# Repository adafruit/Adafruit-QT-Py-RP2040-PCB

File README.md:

## Adafruit QT Py RP2040 PCB

<a href="http://www.adafruit.com/products/4900"><br/>
Click here to purchase one from the Adafruit shop</a>

PCB files for the Adafruit QT Py RP2040.

Format is EagleCAD schematic and board layout
* https://www.adafruit.com/product/4900

### Description

What a cutie pie! Or is it... a QT Py? This diminutive dev board comes with one of our new favorite chip, the RP2040. It's been made famous in the new Raspberry Pi Pico and our Feather RP2040 and ItsyBitsy RP2040, but what if we wanted something really smol?

A new chip means a new QT Py, and the Raspberry Pi RP2040 is no exception. When we saw this chip we thought "this chip is going to be awesome when we give it the cuuutie QT Py Treatment", and so we did! This QT Py features the RP2040, and all niceties you know and love about the original QT Py

#### Plug-and-play STEMMA QT

The star of the QT Py is our favorite connector - the STEMMA QT, a chainable I2C port that can be used with any of our STEMMA QT sensors and accessories. Having this connector means you don't need to do any soldering to get started.

What can you pop into the QT port? How about OLEDs! Inertial Measurment Units! Sensors a-plenty. All plug-and-play thanks to the innovative chainable design: SparkFun Qwiic-compatible STEMMA QT connectors for the I2C bus so you don't even need to solder. Just plug in a compatible cable and attach it to your MCU of choice, and you’re ready to load up some software and measure some light.

Use any SparkFun Qwiic boards! Seeed Grove I2C boards will also work with this adapter cable.

#### Software Support

At the time of launch, there is no Arduino core support for the chip on this board. There is great C/C++ support, an official MicroPython port, and a CircuitPython port! We of course recommend CircuitPython because we think it's the easiest way to get started and it has support with most of our drivers, displays, sensors, and more, supported out of the box so you can follow along with our CircuitPython projects and tutorials.

#### QT Py RP2040 Specifications

Pinout and shape is Seeed Xiao compatible, with castellated pads so you can solder it to a PCB with a cut out to allow the bottom components some breathing room. In addition to the QT connector, we also added an RGB NeoPixel (with a controllable power pin to allow for ultra-low-power usage), and both boot-mode and reset buttons (great for restarting your program or entering the bootloader). This QT Py comes with loose 0.1" headers you can solder in for breadboard use

While the RP2040 has lots of onboard RAM (264KB), it does not have built-in FLASH memory. Instead, that is provided by the external QSPI flash chip. On this board there is 8MB, which is shared between the program it's running and any file storage used by MicroPython or CircuitPython. When using C/C++ you get the whole flash memory, if using Python you will have about 7 MB remaining for code, files, images, fonts, etc.

* Same size, form-factor, and pin-out as our SAMD-based QT Py
* USB Type C connector - If you have only Micro B cables, this adapter will come in handy!
* RP2040 32-bit Cortex M0+ dual-core running at ~125 MHz @ 3.3V logic and power
* 264 KB RAM
* 8 MB SPI FLASH chip for storing files and CircuitPython/MicroPython code storage. No EEPROM
* Native USB supported by every OS - can be used as USB serial console, MIDI, Keyboard/Mouse HID, even a little disk drive for storing Python scripts.
* Can be used with MicroPython or CircuitPython
* Built-in RGB NeoPixel LED
* 13 GPIO pins (11 breakout pads and two QT pads):
  * Four 12 bit ADCs (one more than Pico)
  * Two I2C ports (one on the QT connector, one on the breakout pads)
  * SPI and UART peripherals, in standard QT Py locations,
  * PWM outputs on every IO pin - for servos, LEDs, etc
  * There are 6 GPIO in consecutive order for PIO compatibility
* 3.3V regulator with 600mA peak output
* 12 MHz crystal
* Both Reset button and Bootloader select buttons for quick restarts (no unplugging-replugging to relaunch code)
* Really really small

#### About the RP2040

Inside the RP2040 is a 'permanent ROM' USB UF2 bootloader. What that means is when you want to program new firmware, you can hold down the BOOT button while plugging it into USB (or pulling down the RUN/Reset pin to ground) and it will appear as a USB disk drive you can drag the firmware onto. Folks who have been using Adafruit products will find this very familiar - we use the technique on all our native-USB boards. Just note you don't double-click reset, instead hold down BOOTSEL during boot to enter the bootloader!

The RP2040 is a powerful chip, which has the clock speed of our M4 (SAMD51), and two cores that are equivalent to our M0 (SAMD21). Since it is an M0 chip, it does not have a floating point unit or DSP hardware support - so if you're doing something with heavy floating point math, it will be done in software and thus not as fast as an M4. For many other computational tasks, you'll get close-to-M4 speeds!

For peripherals, there are two I2C controllers, two SPI controllers, and two UARTs that are multiplexed across the GPIO - check the pinout for what pins can be set to which. There are 16 PWM channels, each pin has a channel it can be set to (ditto on the pinout).

You'll note there's no I2S peripheral, or SDIO, or camera, what's up with that? Well, instead of having specific hardware support for serial-data-like peripherals like these, the RP2040 comes with the PIO state machine system which is a unique and powerful way to create custom hardware logic and data processing blocks that run on their own without taking up a CPU. For example, NeoPixels - often we bitbang the timing-specific protocol for these LEDs. For the RP2040, we instead use PIO object that reads in the data buffer and clocks out the right bitstream with perfect accuracy. Same with I2S audio in or out, LED matrix displays, 8-bit or SPI based TFTs, even VGA! In MicroPython and CircuitPython you can create PIO control commands to script the peripheral and load it in at runtime. There are 2 PIO peripherals with 4 state machines each.

### License

Adafruit invests time and resources providing this open source design, please support Adafruit and open-source hardware by purchasing products from [Adafruit](https://www.adafruit.com)!

Designed by Limor Fried/Ladyada for Adafruit Industries.

Creative Commons Attribution/Share-Alike, all text above must be included in any redistribution.
See license.txt for additional details.

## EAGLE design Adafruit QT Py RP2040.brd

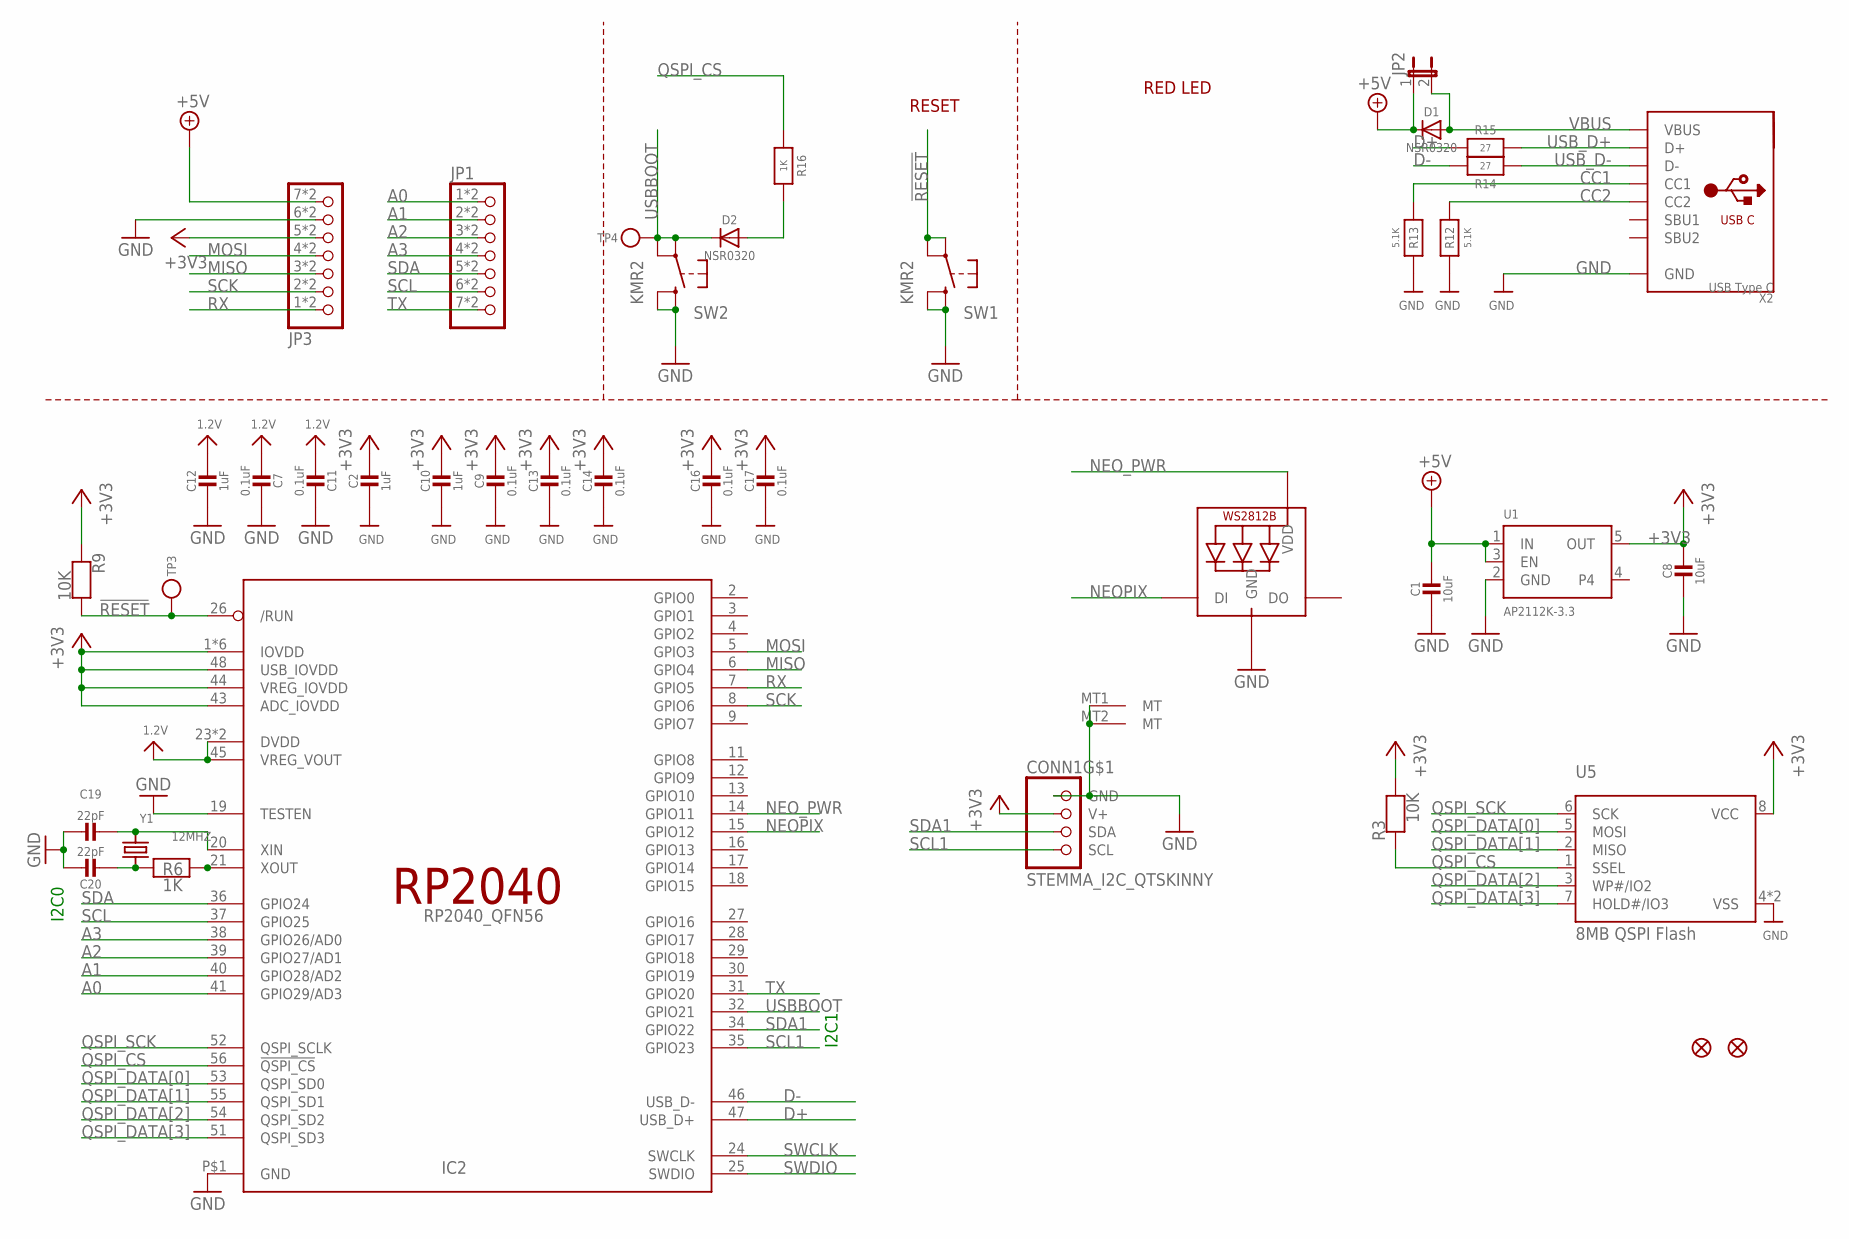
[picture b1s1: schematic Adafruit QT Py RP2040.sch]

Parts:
C1, C8: 10uF; 0805-NO
C2, C10, C12: 1uF; 0603-NO
C7, C9, C11, C13, C14, C16, C17: 0.1uF; _0402NO
C19, C20: 22pF; _0402NO
CONN1: STEMMA_I2C_QTSKINNY; JST_SH4_SKINNY
D1, D2: NSR0320; SOD-323_MINI
IC2: RP2040_QFN56; QFN56_7MM_REDUCEDEPAD
JP1, JP3: HEADER-1X7_CASTEL; 1X07_CASTEL
JP2: JUMPER-2SMD-NO; SJ_2S-NO
LED1: WS2812B_SK6805_1515; SK6805_1515
R3, R9: 10K; _0402NO
R6, R16: 1K; _0402NO
R12, R13: 5.1K; _0402NO
R14, R15: 27; _0402NO
SW1, SW2: KMR2; BTN_KMR2_4.6X2.8
TP3, TP4: TESTPOINTROUND1.5MMNO; TESTPOINT_ROUND_1.5MM_NO
U1: AP2112K-3.3; SOT23-5
U5: 8MB QSPI Flash; USON8_4X4
U$6, U$8: FIDUCIAL_1MM
X2: USB Type C; USB_C_CUSB31-CFM2AX-01-X
Y1: 12MHZ; CRYSTAL_2.5X2

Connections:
1.2V: C7.2, C11.2, C12.1, IC2.23 (DVDD), IC2.45 (VREG_VOUT), IC2.50 (DVDD)
!RESET: IC2.26 (/RUN), R9.2, SW1.A, SW1.A' (P1), TP3.P$1
+3V3: C2.1, C8.1, C9.1, C10.1, C13.1, C14.1, C16.1, C17.1, CONN1.2 (V+), IC2.1 (IOVDD), IC2.10 (IOVDD), IC2.22 (IOVDD), IC2.33 (IOVDD), IC2.42 (IOVDD), IC2.43 (ADC_IOVDD), IC2.44 (VREG_IOVDD), IC2.48 (USB_IOVDD), IC2.49 (IOVDD), JP3.5, JP3.5C (5), R3.2, R9.1, U1.5 (OUT), U5.8 (VCC)
+5V: C1.1, D1.C, JP2.1, JP3.7, JP3.7C (7), U1.1 (IN), U1.3 (EN)
A0: IC2.41 (GPIO29/AD3), JP1.1, JP1.1C (1)
A1: IC2.40 (GPIO28/AD2), JP1.2, JP1.2C (2)
A2: IC2.39 (GPIO27/AD1), JP1.3, JP1.3C (3)
A3: IC2.38 (GPIO26/AD0), JP1.4, JP1.4C (4)
CC1: R13.2, X2.A5 (CC1)
CC2: R12.2, X2.B5 (CC2)
D+: IC2.47 (USB_D+), R15.2
D-: IC2.46 (USB_D-), R14.2
GND: C1.2, C2.2, C7.1, C8.2, C9.2, C10.2, C11.1, C12.2, C13.2, C14.2, C16.2, C17.2, C19.1, C20.1, CONN1.1 (GND), CONN1.MT1 (MT), CONN1.MT2 (MT), IC2.19 (TESTEN), IC2.P$1 (GND), JP3.6, JP3.6C (6), LED1.4 (GND), R12.1, R13.1, SW1.B (S), SW1.B' (S1), SW2.B (S), SW2.B' (S1), U1.2 (GND), U5.4 (VSS), U5.PAD (VSS), X2.A1B12 (GND), X2.B1A12 (GND)
MISO: IC2.6 (GPIO4), JP3.3, JP3.3C (3)
MOSI: IC2.5 (GPIO3), JP3.4, JP3.4C (4)
unnamed: D2.A, R16.2
unnamed: C19.2, IC2.20 (XIN), Y1.3 (2)
unnamed: C20.2, R6.1, Y1.1
unnamed: IC2.21 (XOUT), R6.2
NEOPIX: IC2.15 (GPIO12), LED1.1 (DI)
NEO_PWR: IC2.14 (GPIO11), LED1.2 (VDD)
QSPI_CS: IC2.56 (!QSPI_CS), R3.1, R16.1, U5.1 (SSEL)
QSPI_DATA[0]: IC2.53 (QSPI_SD0), U5.5 (MOSI)
QSPI_DATA[1]: IC2.55 (QSPI_SD1), U5.2 (MISO)
QSPI_DATA[2]: IC2.54 (QSPI_SD2), U5.3 (WP#/IO2)
QSPI_DATA[3]: IC2.51 (QSPI_SD3), U5.7 (HOLD#/IO3)
QSPI_SCK: IC2.52 (QSPI_SCLK), U5.6 (SCK)
RX: IC2.7 (GPIO5), JP3.1, JP3.1C (1)
SCK: IC2.8 (GPIO6), JP3.2, JP3.2C (2)
SCL: IC2.37 (GPIO25), JP1.6, JP1.6C (6)
SCL1: CONN1.4 (SCL), IC2.35 (GPIO23)
SDA: IC2.36 (GPIO24), JP1.5, JP1.5C (5)
SDA1: CONN1.3 (SDA), IC2.34 (GPIO22)
SWCLK: IC2.24 (SWCLK)
SWDIO: IC2.25 (SWDIO)
TX: IC2.31 (GPIO20), JP1.7, JP1.7C (7)
USBBOOT: D2.C, IC2.32 (GPIO21), SW2.A, SW2.A' (P1), TP4.P$1
USB_D+: R15.1, X2.A6 (D+), X2.B6 (D+)
USB_D-: R14.1, X2.A7 (D-), X2.B7 (D-)
VBUS: D1.A, JP2.2, X2.A4B9 (VBUS), X2.B4A9 (VBUS)

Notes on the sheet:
RESET
RED LED
I2C0
I2C1

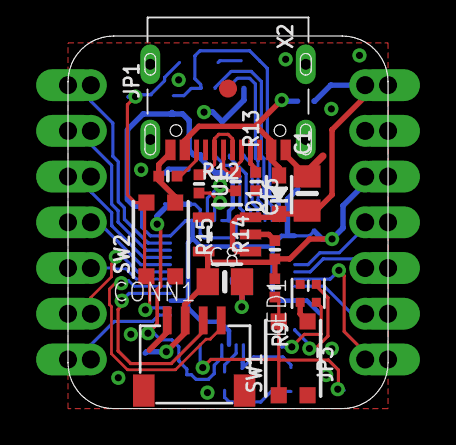
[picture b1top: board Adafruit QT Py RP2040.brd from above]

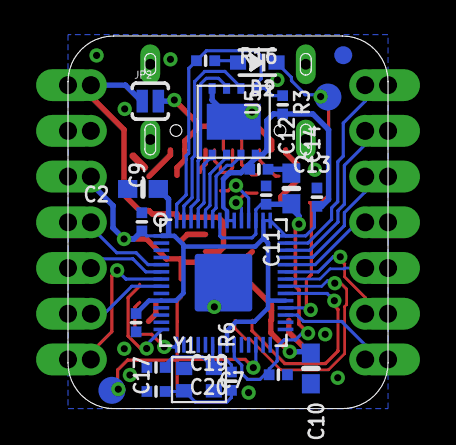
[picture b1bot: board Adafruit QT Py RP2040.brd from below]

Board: 2 copper layers, 17.8 x 20.7 mm, 42 parts (23 on the bottom side), 38 nets.

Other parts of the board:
U$1: QTPICO_BOT
U$2: QTPICO_TOP

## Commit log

2021-04-20 Adding board files.
2021-05-07 Adding pinout file.
2021-12-10 Adding PrettyPins PDF

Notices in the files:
parts and their libraries:
microbuilder: This work is placed in the public domain, and may be freely used for commercial and non-commercial work with the following conditions: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
SparkFun: Licensing: CC v3.0 Share-Alike You are welcome to use this library for commercial purposes.
